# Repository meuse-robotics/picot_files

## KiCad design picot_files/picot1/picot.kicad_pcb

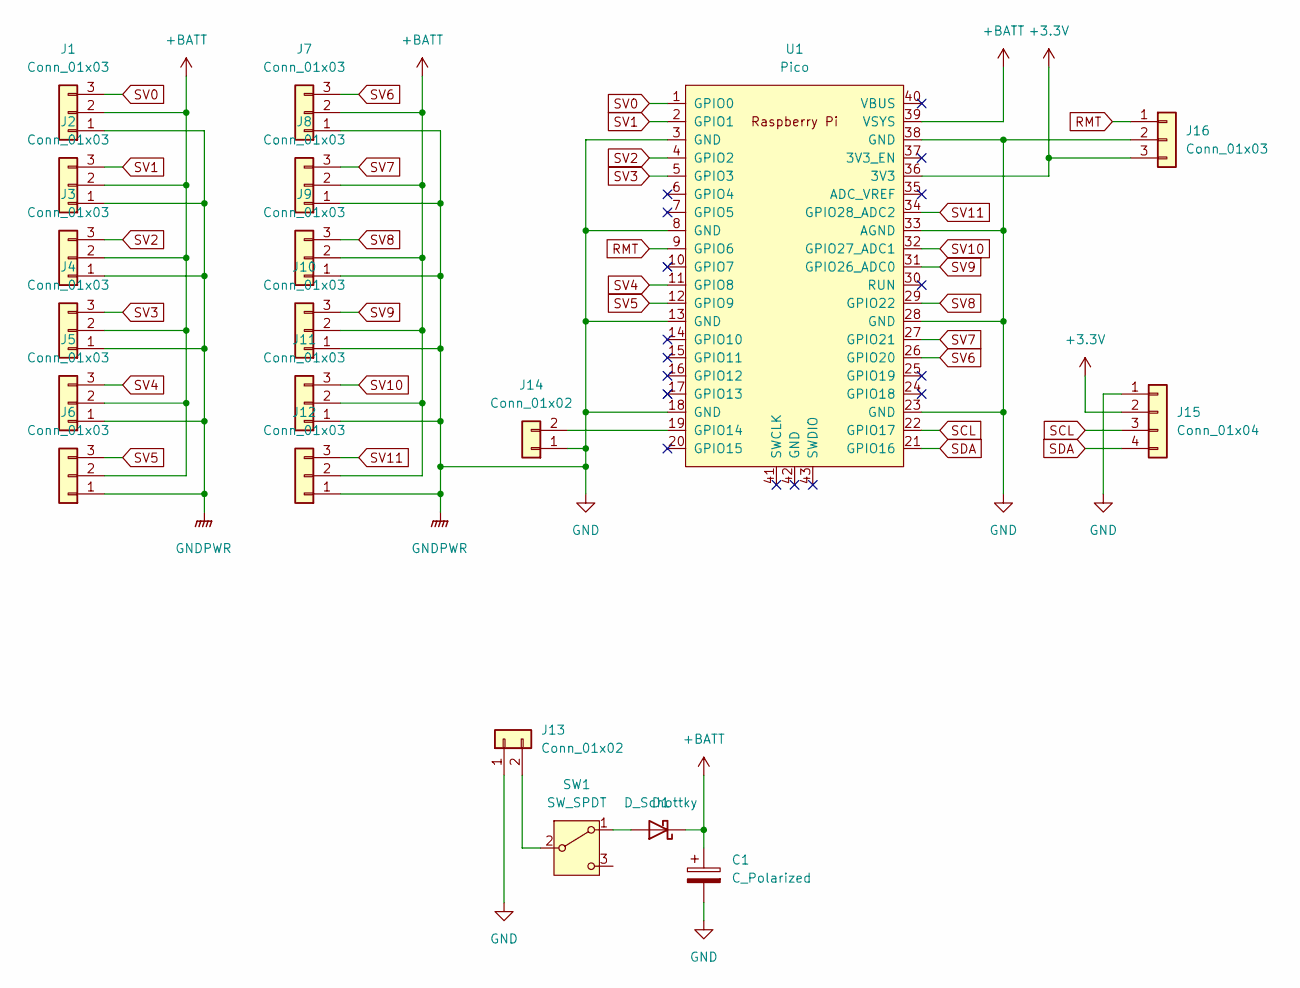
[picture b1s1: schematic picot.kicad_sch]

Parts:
C1: C_Polarized; CP_Radial_D5.0mm_P2.50mm
D1: D_Schottky; D_A-405_P7.62mm_Horizontal
J1, J2, J3, J4, J5, J6, J7, J8, J9, J10, J11, J12, J16: Conn_01x03; PinHeader_1x03_P2.54mm_Vertical
J13: Conn_01x02; PinHeader_1x02_P2.54mm_Vertical
J14: Conn_01x02; Buzzer_TDK_PS1240P02BT_D12.2mm_H6.5mm
J15: Conn_01x04; PinHeader_1x04_P2.54mm_Vertical
SW1: SW_SPDT; PinHeader_1x03_P2.54mm_Vertical
U1: Pico; RPi_Pico_SMD_TH

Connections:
+3.3V: J15.2, J16.3, U1.36 (3V3)
+BATT: C1.1, D1.1 (K), J1.2, J2.2, J3.2, J4.2, J5.2, J6.2, J7.2, J8.2, J9.2, J10.2, J11.2, J12.2, U1.39 (VSYS)
GND: C1.2, J1.1, J2.1, J3.1, J4.1, J5.1, J6.1, J7.1, J8.1, J9.1, J10.1, J11.1, J12.1, J13.1, J14.1, J15.1, J16.2, U1.3 (GND), U1.8 (GND), U1.13 (GND), U1.18 (GND), U1.23 (GND), U1.28 (GND), U1.33 (AGND), U1.38 (GND)
unnamed: D1.2 (A), SW1.1 (A)
unnamed: J13.2, SW1.2 (B)
unnamed: J14.2, U1.19 (GPIO14)
RMT: J16.1, U1.9 (GPIO6)
SCL: J15.3, U1.22 (GPIO17)
SDA: J15.4, U1.21 (GPIO16)
SV0: J1.3, U1.1 (GPIO0)
SV1: J2.3, U1.2 (GPIO1)
SV2: J3.3, U1.4 (GPIO2)
SV3: J4.3, U1.5 (GPIO3)
SV4: J5.3, U1.11 (GPIO8)
SV5: J6.3, U1.12 (GPIO9)
SV6: J7.3, U1.26 (GPIO20)
SV7: J8.3, U1.27 (GPIO21)
SV8: J9.3, U1.29 (GPIO22)
SV9: J10.3, U1.31 (GPIO26_ADC0)
SV10: J11.3, U1.32 (GPIO27_ADC1)
SV11: J12.3, U1.34 (GPIO28_ADC2)

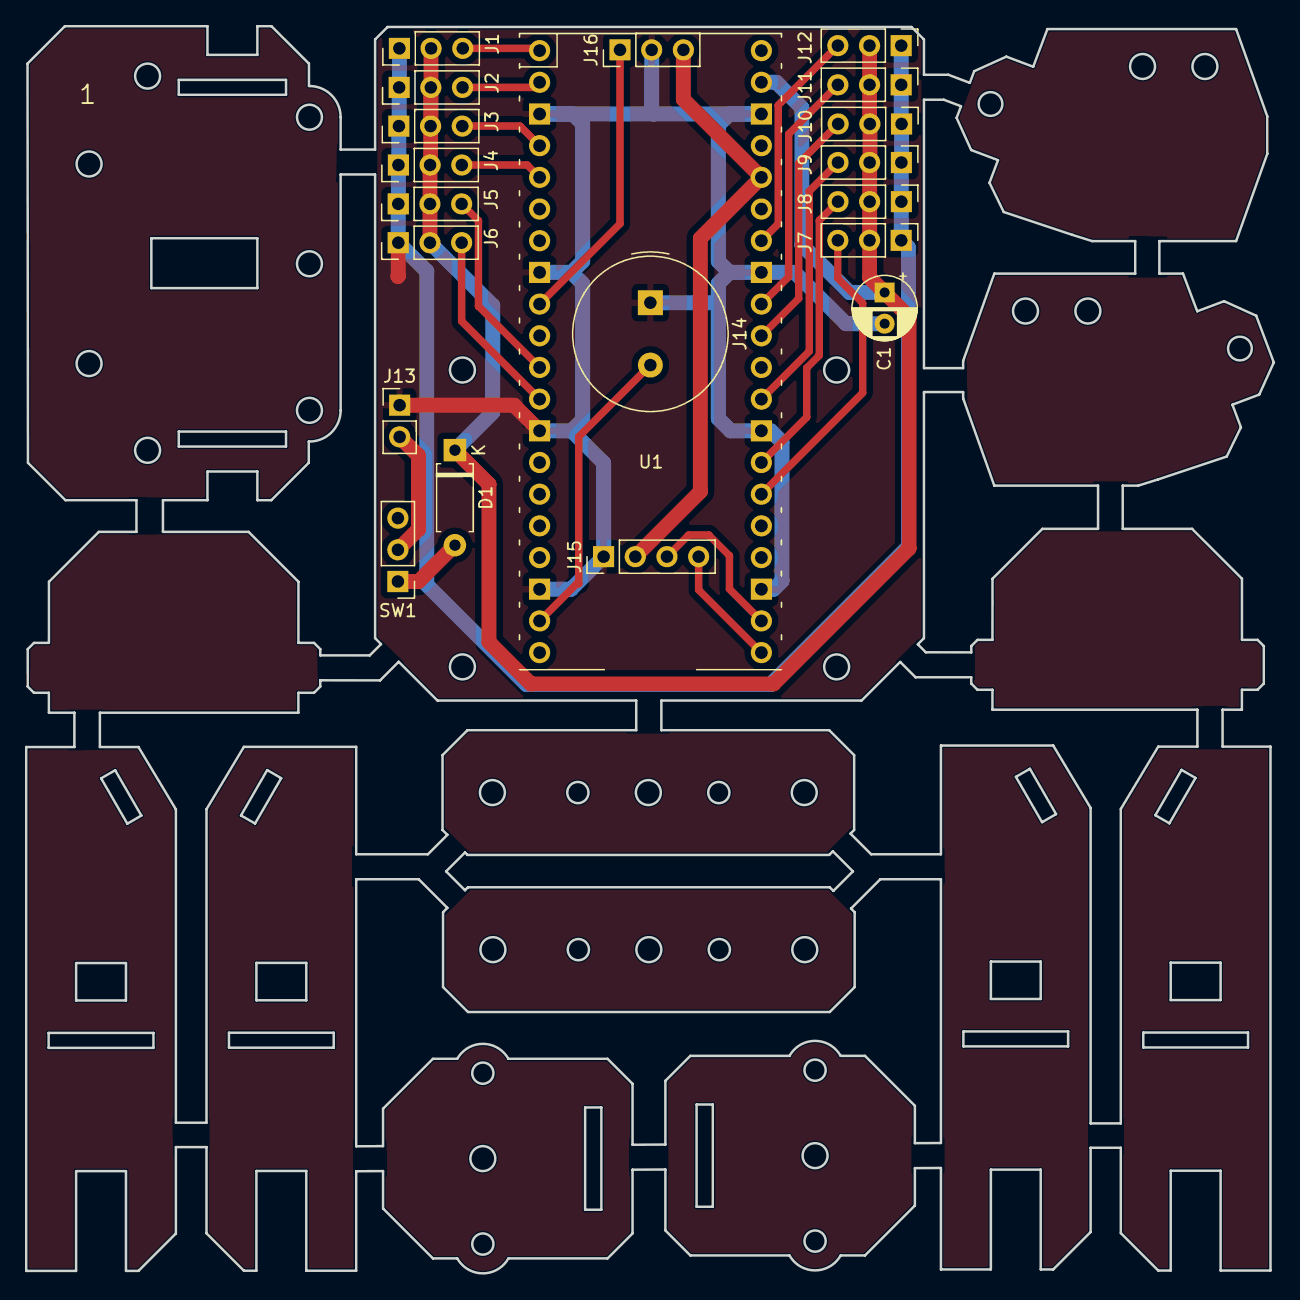
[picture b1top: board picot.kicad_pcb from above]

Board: 2 copper layers, 100.0 x 100.0 mm, 20 parts (0 on the bottom side), 21 nets.

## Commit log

2024-07-05 uploaded
2024-07-06 Create file
